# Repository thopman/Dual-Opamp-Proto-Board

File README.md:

# Dual-Opamp-Proto-Board

Simple soic-8 opamp prototyping board for use with a breadboard. 

Both VCC and VEE have pads for 2 decoupling caps (0805 and 1206, TH is possible too). The VCC, VEE and GND traces have 0805 pads inline for either small value resistors, ferrite beads or you can just jump them with a 0R jumper or solder jumper. 

<------------------------------------------------------------------------------------------------------------------------------->

Copyright (c) 2016 Thomas Hopman

This documentation describes Open Hardware and is licensed under the
CERN OHL v. 1.2.
You may redistribute and modify this documentation under the terms of the
CERN OHL v.1.2. (http://ohwr.org/cernohl). This documentation is distributed
WITHOUT ANY EXPRESS OR IMPLIED WARRANTY, INCLUDING OF
MERCHANTABILITY, SATISFACTORY QUALITY AND FITNESS FOR A
PARTICULAR PURPOSE. Please see the CERN OHL v.1.2 for applicable
conditions

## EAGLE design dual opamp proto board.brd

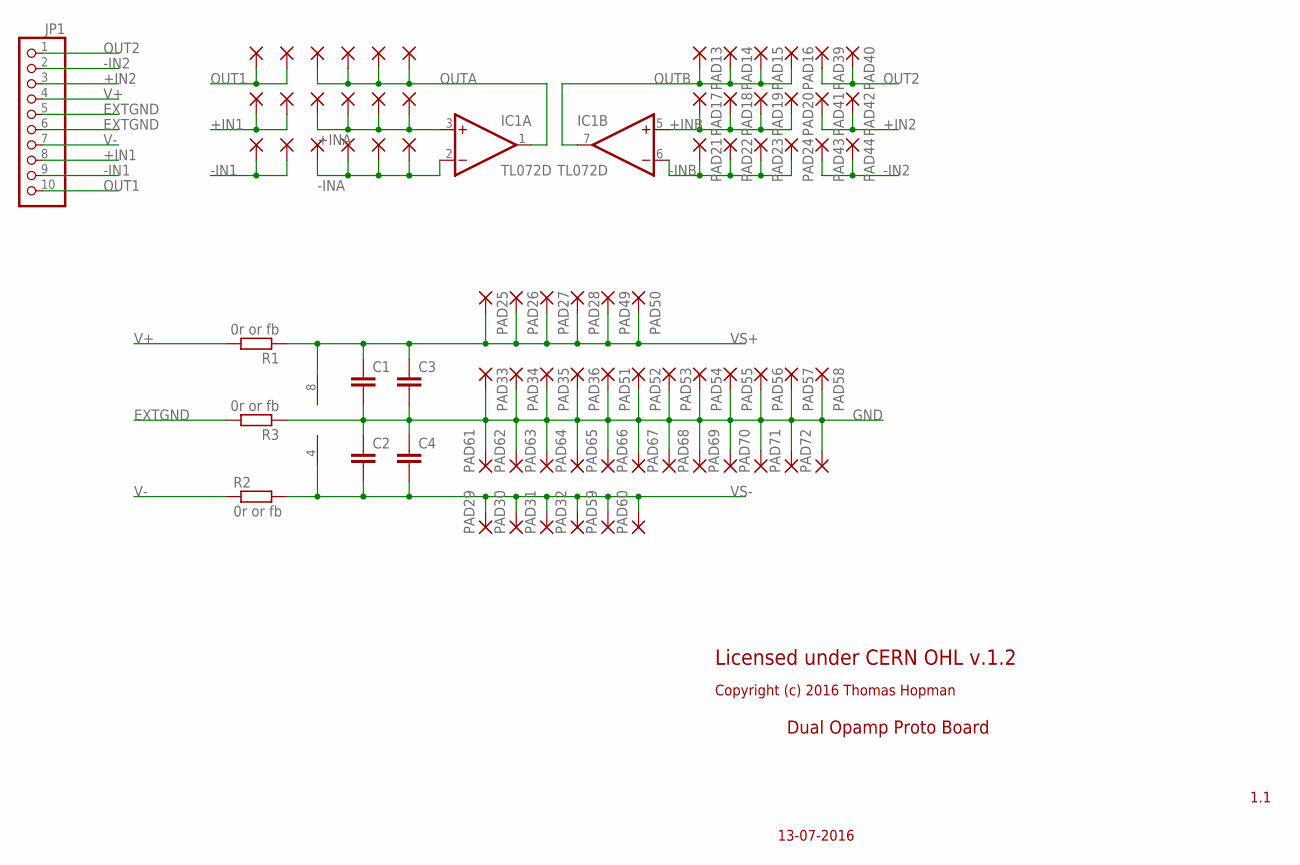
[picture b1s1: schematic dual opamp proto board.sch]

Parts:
C1, C2: C-EUC0805; C0805
C3, C4: C-EUC1206; C1206
IC1: TL072D; SO08
JP1: PINHD-1X10; 1X10
PAD1, PAD2, PAD3, PAD4, PAD5, PAD6, PAD7, PAD8, PAD9, PAD10, PAD11, PAD12, PAD13, PAD14, PAD15, PAD16, PAD17, PAD18, PAD19, PAD20, PAD21, PAD22, PAD23, PAD24, PAD25, PAD26, PAD27, PAD28, PAD29, PAD30, PAD31, PAD32, PAD33, PAD34, PAD35, PAD36, PAD37, PAD38, PAD39, PAD40, PAD41, PAD42, PAD43, PAD44, PAD45, PAD46, PAD47, PAD48, PAD49, PAD50, PAD51, PAD52, PAD53, PAD54, PAD55, PAD56, PAD57, PAD58, PAD59, PAD60, PAD61, PAD62, PAD63, PAD64, PAD65, PAD66, PAD67, PAD68, PAD69, PAD70, PAD71, PAD72: 2,15/1,0
R1, R2, R3: 0r or fb; R0805

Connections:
+IN1: JP1.8, PAD45.1, PAD46.1
+IN2: JP1.3, PAD41.1, PAD42.1
+INA: IC1.3 (+IN), PAD5.1, PAD6.1, PAD7.1, PAD8.1
+INB: IC1.5 (+IN), PAD17.1, PAD18.1, PAD19.1, PAD20.1
-IN1: JP1.9, PAD47.1, PAD48.1
-IN2: JP1.2, PAD43.1, PAD44.1
-INA: IC1.2 (-IN), PAD9.1, PAD10.1, PAD11.1, PAD12.1
-INB: IC1.6 (-IN), PAD21.1, PAD22.1, PAD23.1, PAD24.1
EXTGND: JP1.5, JP1.6, R3.2
GND: C1.2, C2.1, C3.2, C4.1, PAD33.1, PAD34.1, PAD35.1, PAD36.1, PAD51.1, PAD52.1, PAD53.1, PAD54.1, PAD55.1, PAD56.1, PAD57.1, PAD58.1, PAD61.1, PAD62.1, PAD63.1, PAD64.1, PAD65.1, PAD66.1, PAD67.1, PAD68.1, PAD69.1, PAD70.1, PAD71.1, PAD72.1, R3.1
OUT1: JP1.10, PAD37.1, PAD38.1
OUT2: JP1.1, PAD39.1, PAD40.1
OUTA: IC1.1 (OUT), PAD1.1, PAD2.1, PAD3.1, PAD4.1
OUTB: IC1.7 (OUT), PAD13.1, PAD14.1, PAD15.1, PAD16.1
V+: JP1.4, R1.2
V-: JP1.7, R2.1
VS+: C1.1, C3.1, IC1.8 (V+), PAD25.1, PAD26.1, PAD27.1, PAD28.1, PAD49.1, PAD50.1, R1.1
VS-: C2.2, C4.2, IC1.4 (V-), PAD29.1, PAD30.1, PAD31.1, PAD32.1, PAD59.1, PAD60.1, R2.2

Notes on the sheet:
13-07-2016
Dual Opamp Proto Board
1.1
Licensed under CERN OHL v.1.2
Copyright (c) 2016 Thomas Hopman

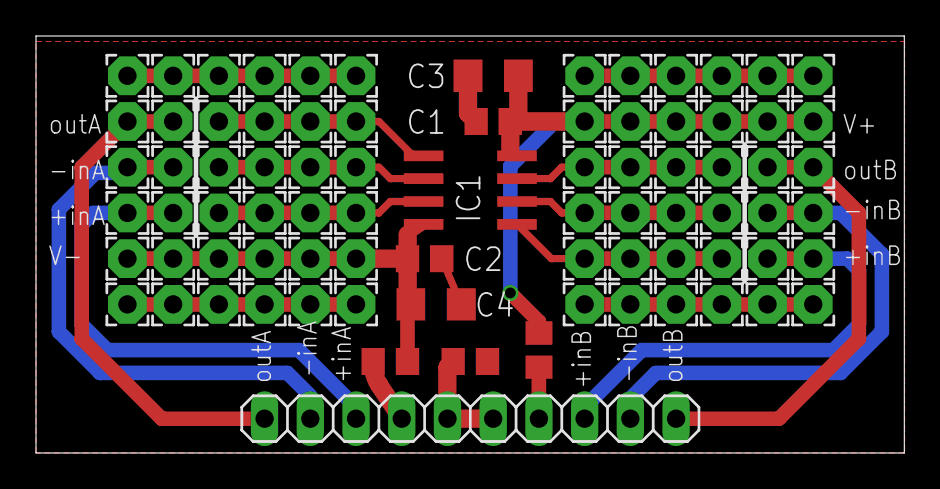
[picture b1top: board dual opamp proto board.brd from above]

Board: 2 copper layers, 48.2 x 23.2 mm, 81 parts (0 on the bottom side), 18 nets.

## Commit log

2016-07-13 Update README.md
    spelling.....
2016-07-13 Adding in Cern Licence, design files and pdf renders.
2016-07-13 Update README.md
    added image.

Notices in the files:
dual opamp proto board.brd:
Copyright 2016 Thomas Hopman
